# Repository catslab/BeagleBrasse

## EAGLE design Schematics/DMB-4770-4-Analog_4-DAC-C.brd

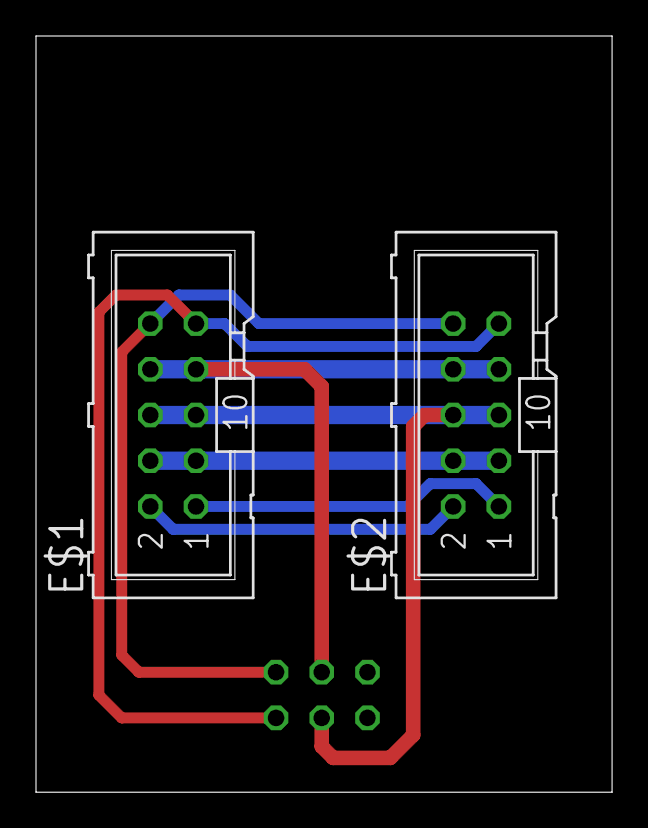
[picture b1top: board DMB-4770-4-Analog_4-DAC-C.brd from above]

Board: 2 copper layers, 32.0 x 42.0 mm, 3 parts (1 on the bottom side), 7 nets.

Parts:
E$1, E$2: ML10
E$3: ML6

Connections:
3V3: E$1.7, E$1.8, E$2.7, E$2.8, E$3.4
5V: E$1.3, E$1.4, E$2.3, E$2.4
GND: E$1.5, E$1.6, E$2.5, E$2.6, E$3.3
S$4: E$1.1, E$2.1
S$5: E$1.2, E$2.2
SCL: E$1.10, E$2.10, E$3.6
SDA: E$1.9, E$2.9, E$3.5

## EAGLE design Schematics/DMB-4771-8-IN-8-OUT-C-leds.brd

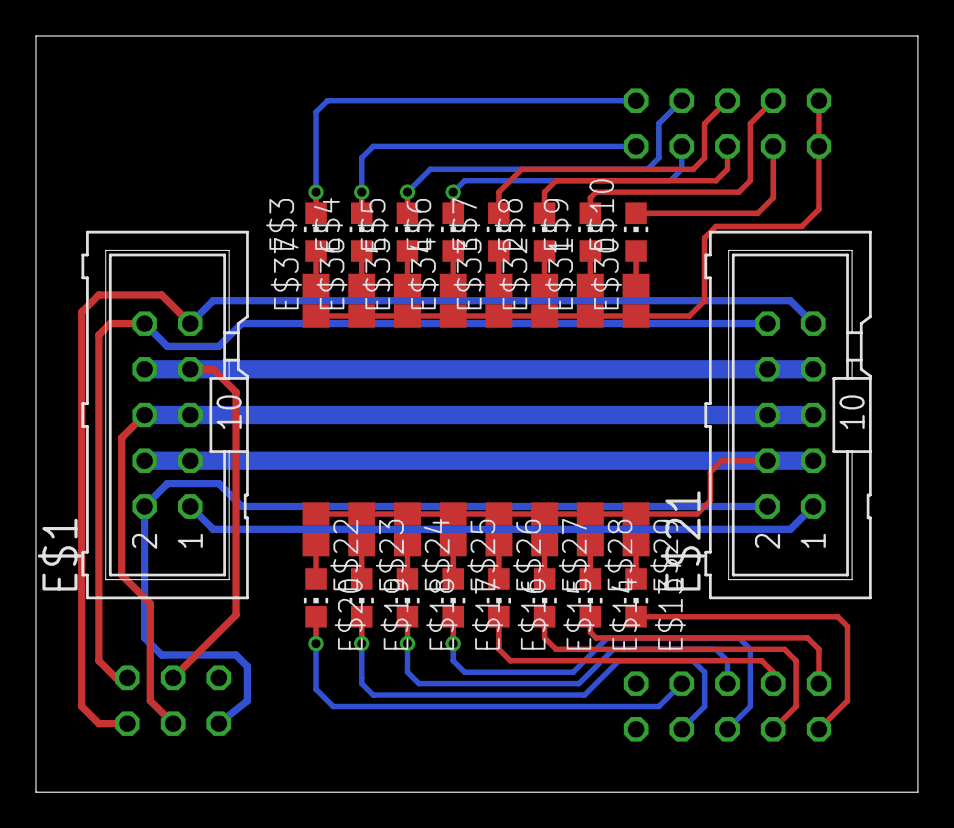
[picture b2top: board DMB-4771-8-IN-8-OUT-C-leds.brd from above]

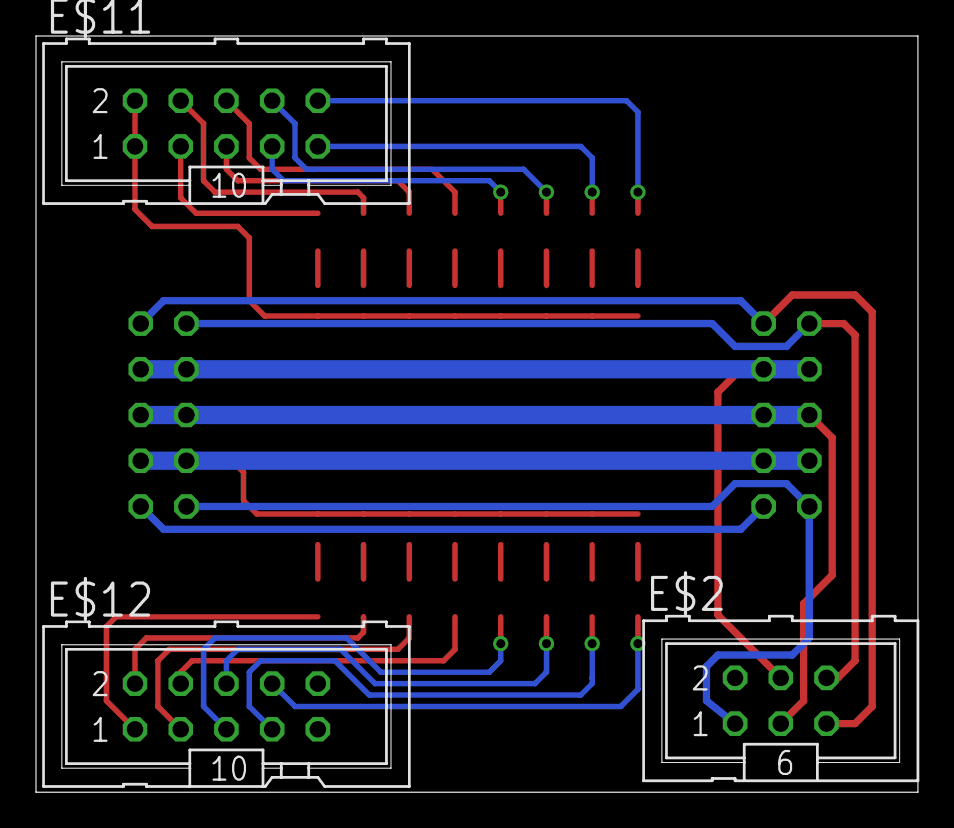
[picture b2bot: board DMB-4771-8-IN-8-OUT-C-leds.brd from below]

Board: 2 copper layers, 49.0 x 42.0 mm, 37 parts (3 on the bottom side), 40 nets.

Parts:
E$1, E$11, E$12, E$21: ML10
E$2: ML6
E$3, E$4, E$5, E$6, E$7, E$8, E$9, E$10, E$13, E$14, E$15, E$16, E$17, E$18, E$19, E$20: CHIP-LED0805
E$22, E$23, E$24, E$25, E$26, E$27, E$28, E$29, E$30, E$31, E$32, E$33, E$34, E$35, E$36, E$37: R0805

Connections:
S$8: E$1.7, E$1.8, E$2.4, E$21.7, E$21.8
S$26: E$1.3, E$1.4, E$21.3, E$21.4, E$22.1, E$23.1, E$24.1, E$25.1, E$26.1, E$27.1, E$28.1, E$29.1
S$27: E$12.8, E$20.C
S$28: E$12.7, E$19.C
S$29: E$12.6, E$18.C
S$34: E$12.5, E$17.C
S$35: E$12.4, E$16.C
S$36: E$12.3, E$15.C
S$37: E$12.2, E$14.C
S$38: E$12.1, E$13.C
S$39: E$20.A, E$22.2
S$40: E$19.A, E$23.2
S$41: E$18.A, E$24.2
S$42: E$17.A, E$25.2
S$43: E$16.A, E$26.2
S$44: E$15.A, E$27.2
S$45: E$14.A, E$28.2
S$46: E$13.A, E$29.2
S$80: E$1.10, E$2.6, E$21.10
S$81: E$3.C, E$11.10
S$83: E$10.A, E$30.2
S$84: E$1.9, E$2.5, E$21.9
S$85: E$9.A, E$31.2
S$86: E$8.A, E$32.2
S$88: E$1.5, E$1.6, E$2.3, E$21.5, E$21.6
S$89: E$7.A, E$33.2
S$90: E$1.2, E$2.1, E$21.2
S$91: E$1.1, E$21.1
S$92: E$6.A, E$34.2
S$93: E$5.A, E$35.2
S$94: E$4.A, E$36.2
S$95: E$3.A, E$37.2
S$96: E$4.C, E$11.9
S$97: E$5.C, E$11.8
S$98: E$6.C, E$11.7
S$99: E$7.C, E$11.6
S$100: E$8.C, E$11.5
S$102: E$9.C, E$11.4
S$103: E$10.C, E$11.3
S$104: E$11.1, E$11.2, E$30.1, E$31.1, E$32.1, E$33.1, E$34.1, E$35.1, E$36.1, E$37.1

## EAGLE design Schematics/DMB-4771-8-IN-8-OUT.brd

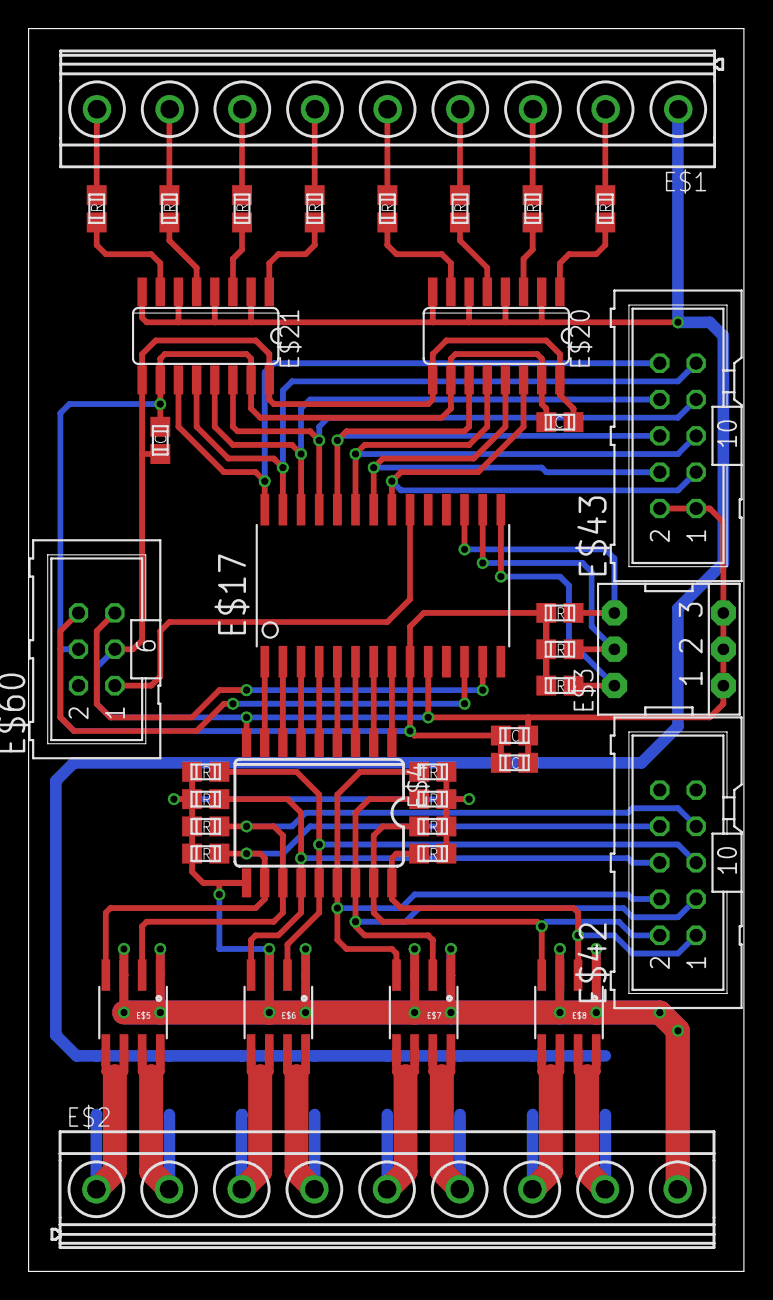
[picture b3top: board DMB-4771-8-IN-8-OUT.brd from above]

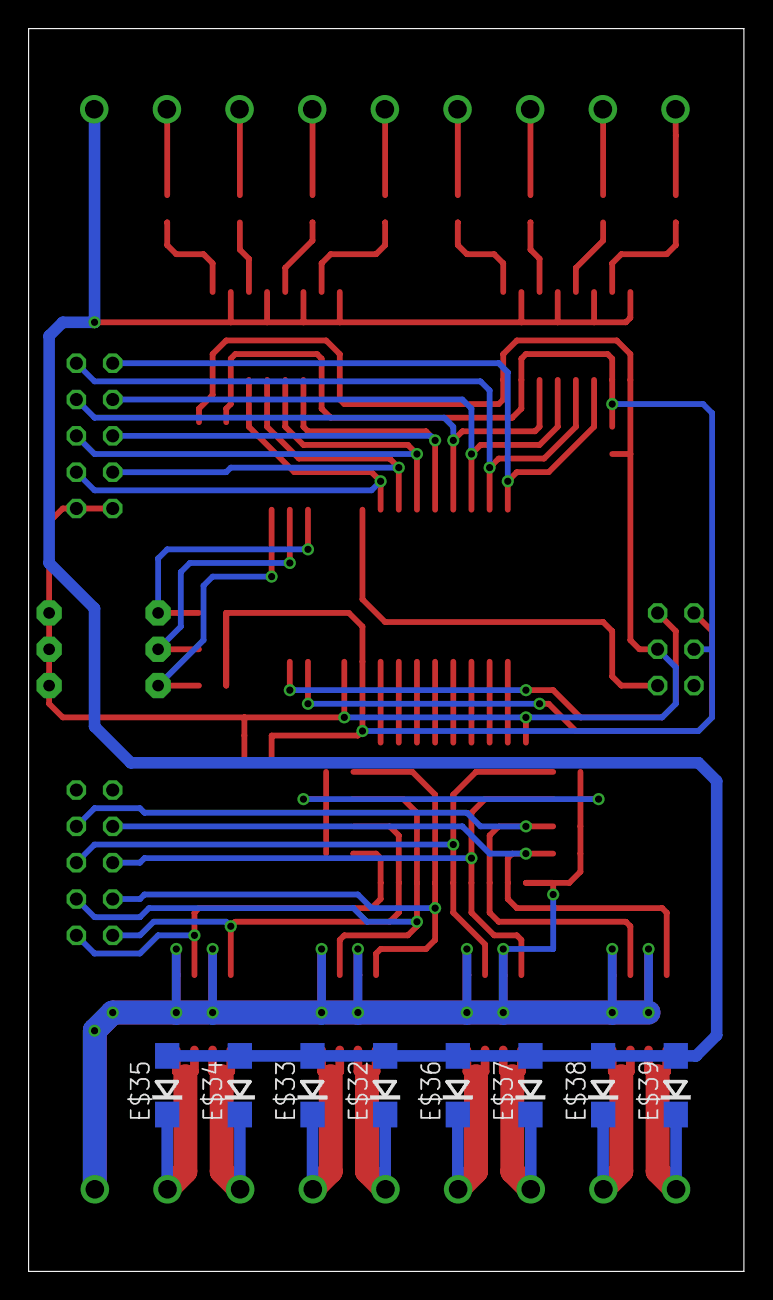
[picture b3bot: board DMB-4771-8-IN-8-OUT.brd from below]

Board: 2 copper layers, 50.0 x 86.9 mm, 45 parts (8 on the bottom side), 58 nets.

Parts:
E$1, E$2: MKDSN1,5/9-5,08
E$3: EPG-03-SMALL
E$4: ULN2803; SO18L
E$5, E$6, E$7, E$8: SOIC8
E$9, E$10, E$11, E$12, E$13, E$14, E$15, E$16, E$18, E$19, E$226: 10K; R0805
E$17: MCP23017; SO28-3
E$20, E$21: ACSL-6400; SO16
E$22, E$23, E$24, E$25, E$26, E$27, E$28, E$29: 1.30K; R0805
E$30, E$40, E$41: 100n; C0805
E$31: 1u; C0805
E$32, E$33, E$34, E$35, E$36, E$37, E$38, E$39: DO214AC
E$42, E$43: ML10
E$60: ML6

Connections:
3V3: E$16.1, E$17.9, E$18.1, E$19.1, E$20.10, E$20.15, E$21.10, E$21.15, E$30.1, E$31.1, E$40.2, E$41.2, E$60.4
GND: E$3.1, E$3.2, E$3.3, E$4.9, E$17.10, E$20.9, E$20.16, E$21.9, E$21.16, E$30.2, E$31.2, E$40.1, E$41.1, E$43.1, E$43.2, E$60.3
INT1: E$17.20, E$60.1
POWER_GND: E$1.1, E$20.2, E$20.4, E$20.6, E$20.8, E$21.2, E$21.4, E$21.6, E$21.8, E$32.A, E$33.A, E$34.A, E$35.A, E$36.A, E$37.A, E$38.A, E$39.A
S$9: E$2.9, E$4.10, E$5.1, E$5.3, E$6.1, E$6.3, E$7.1, E$7.3, E$8.1, E$8.3, E$9.1, E$10.1, E$11.1, E$12.2, E$13.2, E$14.2, E$15.2, E$226.1
S$11: E$2.1, E$5.5, E$5.6, E$39.C
S$13: E$2.2, E$5.7, E$5.8, E$38.C
S$14: E$2.3, E$6.5, E$6.6, E$37.C
S$15: E$17.28, E$21.11, E$43.10
S$16: E$2.5, E$7.5, E$7.6, E$32.C
S$20: E$4.11, E$5.4, E$42.8, E$226.2
S$21: E$4.12, E$5.2, E$9.2, E$42.7
S$23: E$4.13, E$6.4, E$10.2, E$42.6
S$25: E$4.14, E$6.2, E$11.2, E$42.5
S$28: E$4.15, E$7.4, E$12.1, E$42.4
S$29: E$4.16, E$7.2, E$13.1, E$42.3
S$31: E$4.17, E$8.4, E$14.1, E$42.2
S$32: E$4.18, E$8.2, E$15.1, E$42.1
S$33: E$4.8, E$17.1
S$34: E$4.7, E$17.2
S$35: E$4.6, E$17.3
S$38: E$4.5, E$17.4
S$39: E$4.4, E$17.5
S$40: E$4.3, E$17.6
S$41: E$4.2, E$17.7
S$42: E$4.1, E$17.8
S$55: E$3.4, E$17.17, E$18.2
S$59: E$3.5, E$16.2, E$17.16
S$66: E$3.6, E$17.15, E$19.2
S$67: E$2.6, E$7.7, E$7.8, E$33.C
S$68: E$2.7, E$8.5, E$8.6, E$34.C
S$70: E$2.8, E$8.7, E$8.8, E$35.C
S$71: E$2.4, E$6.7, E$6.8, E$36.C
S$74: E$21.7, E$22.1
S$75: E$21.5, E$23.1
S$76: E$21.3, E$24.1
S$77: E$1.9, E$22.2
S$78: E$1.8, E$23.2
S$79: E$1.7, E$24.2
S$80: E$1.6, E$25.2
S$81: E$1.5, E$26.2
S$82: E$1.4, E$27.2
S$83: E$1.3, E$28.2
S$84: E$1.2, E$29.2
S$85: E$21.1, E$25.1
S$86: E$20.7, E$26.1
S$90: E$17.27, E$21.12, E$43.9
S$91: E$17.26, E$21.13, E$43.8
S$92: E$17.25, E$21.14, E$43.7
S$93: E$17.24, E$20.11, E$43.6
S$94: E$17.23, E$20.12, E$43.5
S$95: E$17.22, E$20.13, E$43.4
S$96: E$17.21, E$20.14, E$43.3
S$97: E$20.5, E$27.1
S$98: E$20.3, E$28.1
S$99: E$20.1, E$29.1
SCL: E$17.12, E$60.6
SDA: E$17.13, E$60.5

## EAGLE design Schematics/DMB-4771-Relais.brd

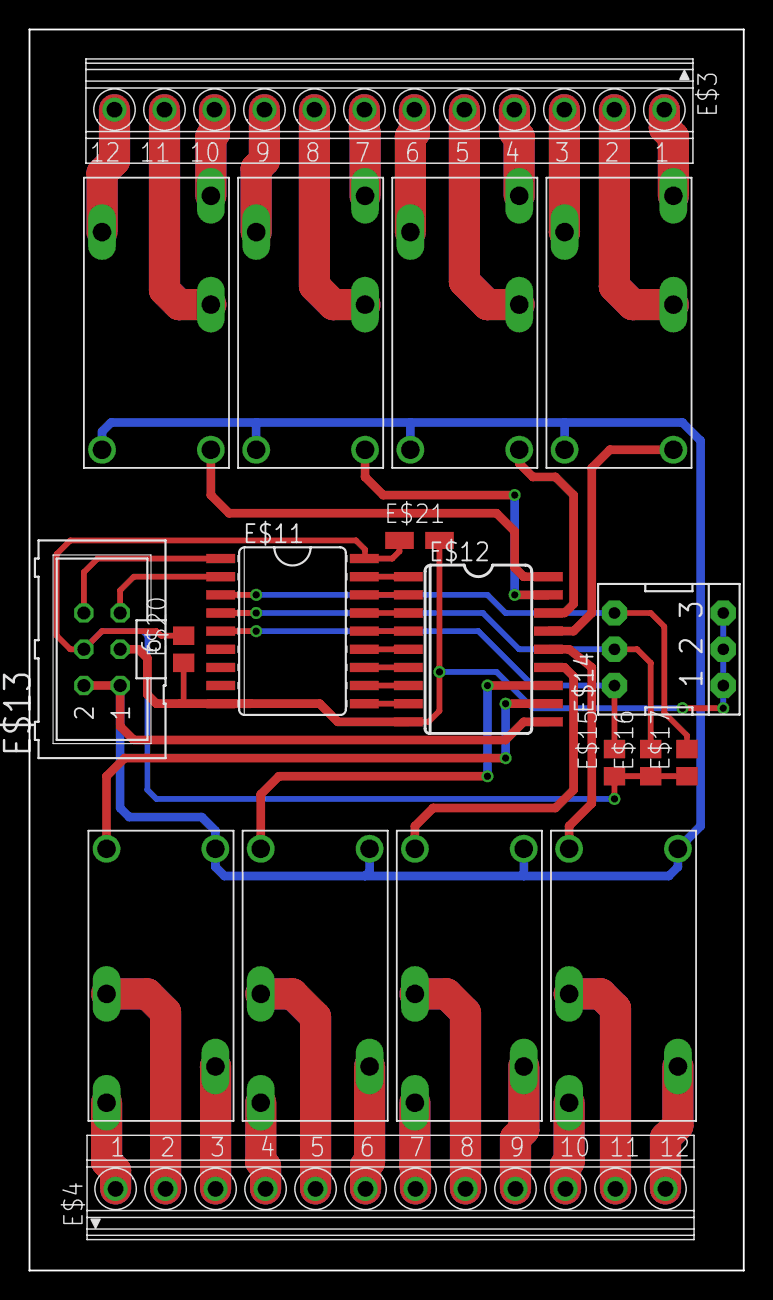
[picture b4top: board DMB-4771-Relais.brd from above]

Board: 2 copper layers, 50.0 x 86.9 mm, 19 parts (0 on the bottom side), 48 nets.

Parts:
E$1, E$2, E$5, E$6, E$7, E$8, E$9, E$10: ALQ105; ALQ
E$3, E$4: 175317
E$11: MCP2308; SO18W
E$12: ULN2803; SO18L
E$13: ML6
E$14: EPG-03-SMALL
E$15, E$16, E$17: 10K; R0805
E$20: 100n; R0805
E$21: 10u; CT3216

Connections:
3V3: E$11.18, E$13.4, E$15.1, E$16.1, E$17.1, E$20.2, E$21.+
5V: E$1.P$1, E$2.P$1, E$5.P$1, E$6.P$1, E$7.P$1, E$8.P$1, E$9.P$1, E$10.P$1, E$12.10, E$13.1, E$13.2
GND: E$11.9, E$12.9, E$13.3, E$14.1, E$14.2, E$14.3, E$20.1, E$21.-
S$8: E$2.P$5, E$3.21
S$9: E$2.P$3, E$3.20
S$10: E$2.P$4, E$3.19
S$11: E$1.P$5, E$3.9
S$13: E$1.P$4, E$3.7
S$14: E$1.P$3, E$3.8
S$15: E$3.6, E$6.P$5
S$16: E$3.5, E$6.P$3
S$17: E$3.4, E$6.P$4
S$18: E$3.3, E$5.P$5
S$19: E$3.2, E$5.P$3
S$20: E$3.1, E$5.P$4
S$21: E$4.21, E$8.P$5
S$22: E$4.20, E$8.P$3
S$23: E$4.19, E$8.P$4
S$24: E$4.8, E$7.P$3
S$25: E$4.6, E$10.P$5
S$26: E$4.5, E$10.P$3
S$27: E$4.3, E$9.P$5
S$28: E$4.2, E$9.P$3
S$29: E$4.9, E$7.P$5
S$30: E$4.7, E$7.P$4
S$31: E$4.4, E$10.P$4
S$32: E$4.1, E$9.P$4
S$61: E$11.17, E$12.1
S$62: E$11.16, E$12.2
S$63: E$11.15, E$12.3
S$64: E$11.14, E$12.4
S$65: E$11.13, E$12.5
S$66: E$11.12, E$12.6
S$67: E$11.11, E$12.7
S$68: E$11.10, E$12.8
S$70: E$2.P$2, E$12.18
S$71: E$1.P$2, E$12.17
S$72: E$6.P$2, E$12.16
S$73: E$5.P$2, E$12.15
S$74: E$8.P$2, E$12.14
S$75: E$7.P$2, E$12.13
S$76: E$10.P$2, E$12.12
S$77: E$9.P$2, E$12.11
S$78: E$11.3, E$14.4, E$17.2
S$79: E$11.4, E$14.5, E$16.2
S$80: E$11.5, E$14.6, E$15.2
SCL: E$11.1, E$13.6
SDA: E$11.2, E$13.5

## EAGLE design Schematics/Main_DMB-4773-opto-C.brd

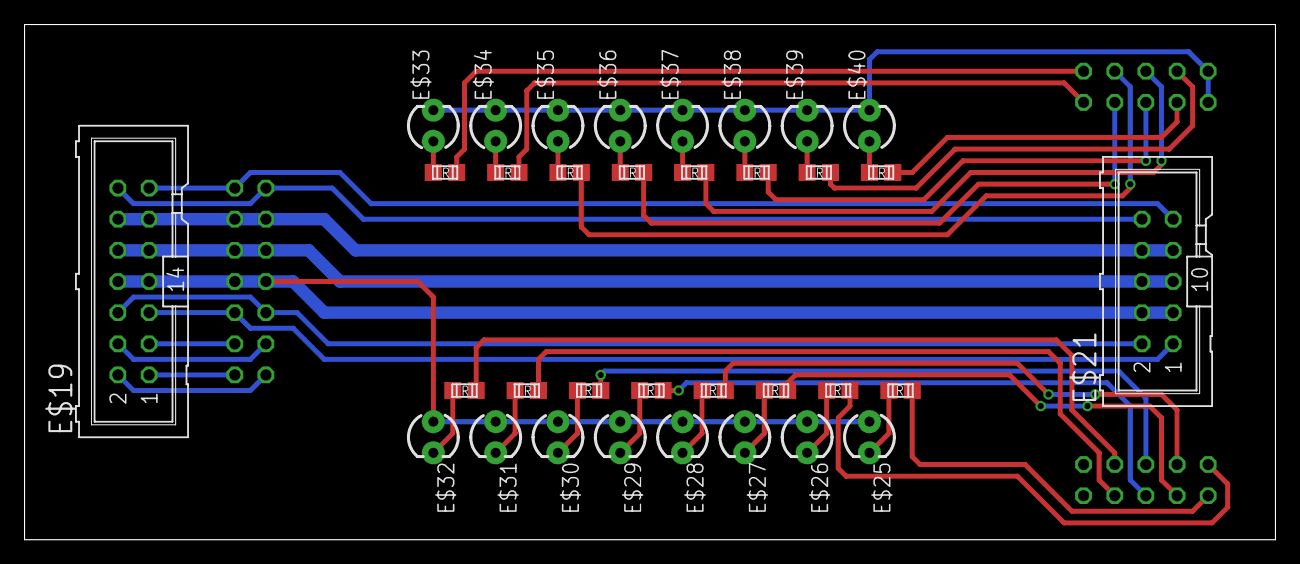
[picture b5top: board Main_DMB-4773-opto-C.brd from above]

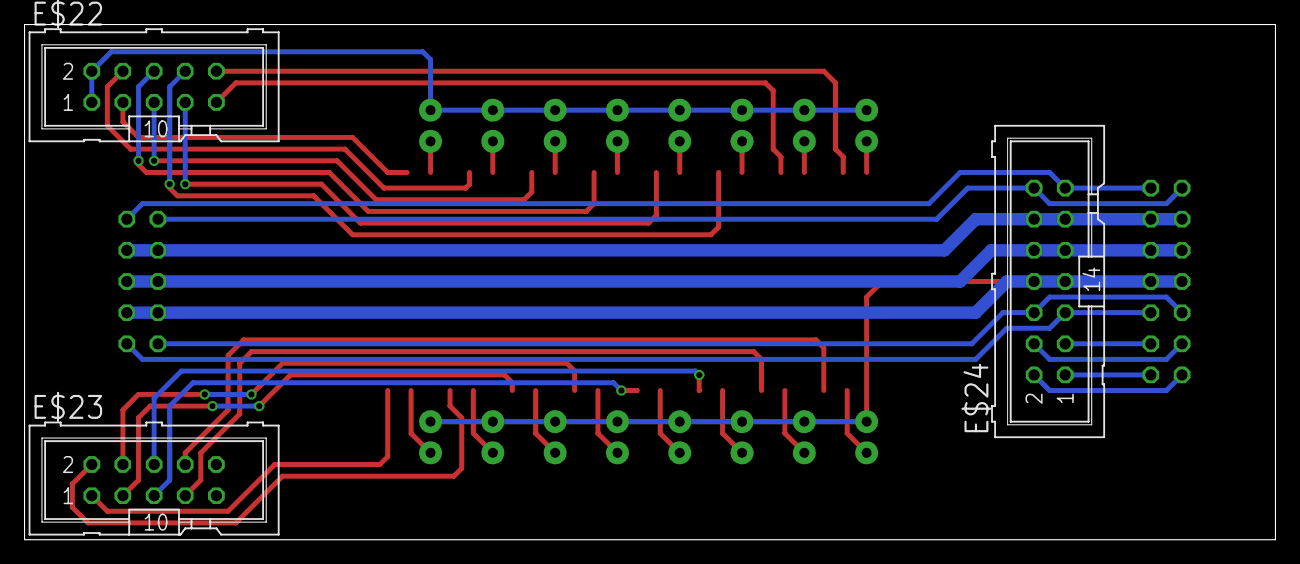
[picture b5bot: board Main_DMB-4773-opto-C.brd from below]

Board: 2 copper layers, 102.0 x 42.0 mm, 37 parts (3 on the bottom side), 44 nets.

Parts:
E$19, E$24: ML14
E$21, E$22, E$23: ML10
E$25, E$26, E$27, E$28, E$29, E$30, E$31, E$32, E$33, E$34, E$35, E$36, E$37, E$38, E$39, E$40: LED3MM
E$41, E$42, E$43, E$44, E$45, E$46, E$47, E$48, E$51, E$75, E$93, E$94, E$95, E$96, E$97, E$98: 470; R0805

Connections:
S$86: E$19.11, E$19.12, E$21.7, E$21.8, E$24.11, E$24.12
S$88: E$19.9, E$19.10, E$21.5, E$21.6, E$24.9, E$24.10
S$90: E$19.6, E$21.2, E$24.6
S$91: E$19.5, E$21.1, E$24.5
S$92: E$19.4, E$24.4
S$93: E$19.3, E$24.3
S$94: E$19.2, E$24.2
S$95: E$19.1, E$24.1
S$96: E$23.4, E$45.1
S$97: E$19.7, E$19.8, E$21.3, E$21.4, E$24.7, E$24.8, E$25.A, E$26.A, E$27.A, E$28.A, E$29.A, E$30.A, E$31.A, E$32.A
S$98: E$32.K, E$41.1
S$100: E$23.8, E$41.2
S$103: E$31.K, E$42.1
S$104: E$23.7, E$42.2
S$106: E$30.K, E$43.2
S$107: E$29.K, E$44.2
S$109: E$23.6, E$43.1
S$110: E$23.5, E$44.1
S$111: E$23.3, E$46.1
S$112: E$23.2, E$47.1
S$113: E$23.1, E$48.1
S$115: E$28.K, E$45.2
S$117: E$27.K, E$46.2
S$118: E$26.K, E$47.2
S$121: E$25.K, E$48.2
S$122: E$22.10, E$51.2
S$123: E$22.9, E$75.2
S$124: E$22.8, E$93.2
S$125: E$22.7, E$94.2
S$127: E$22.6, E$95.2
S$128: E$22.5, E$96.2
S$129: E$22.4, E$97.2
S$130: E$22.3, E$98.2
S$131: E$22.1, E$22.2, E$33.K, E$34.K, E$35.K, E$36.K, E$37.K, E$38.K, E$39.K, E$40.K
S$135: E$33.A, E$51.1
S$136: E$34.A, E$75.1
S$137: E$35.A, E$93.1
S$138: E$36.A, E$94.1
S$139: E$37.A, E$95.1
S$140: E$38.A, E$96.1
S$142: E$39.A, E$97.1
S$144: E$40.A, E$98.1
SCL: E$19.14, E$21.10, E$24.14
SDA: E$19.13, E$21.9, E$24.13

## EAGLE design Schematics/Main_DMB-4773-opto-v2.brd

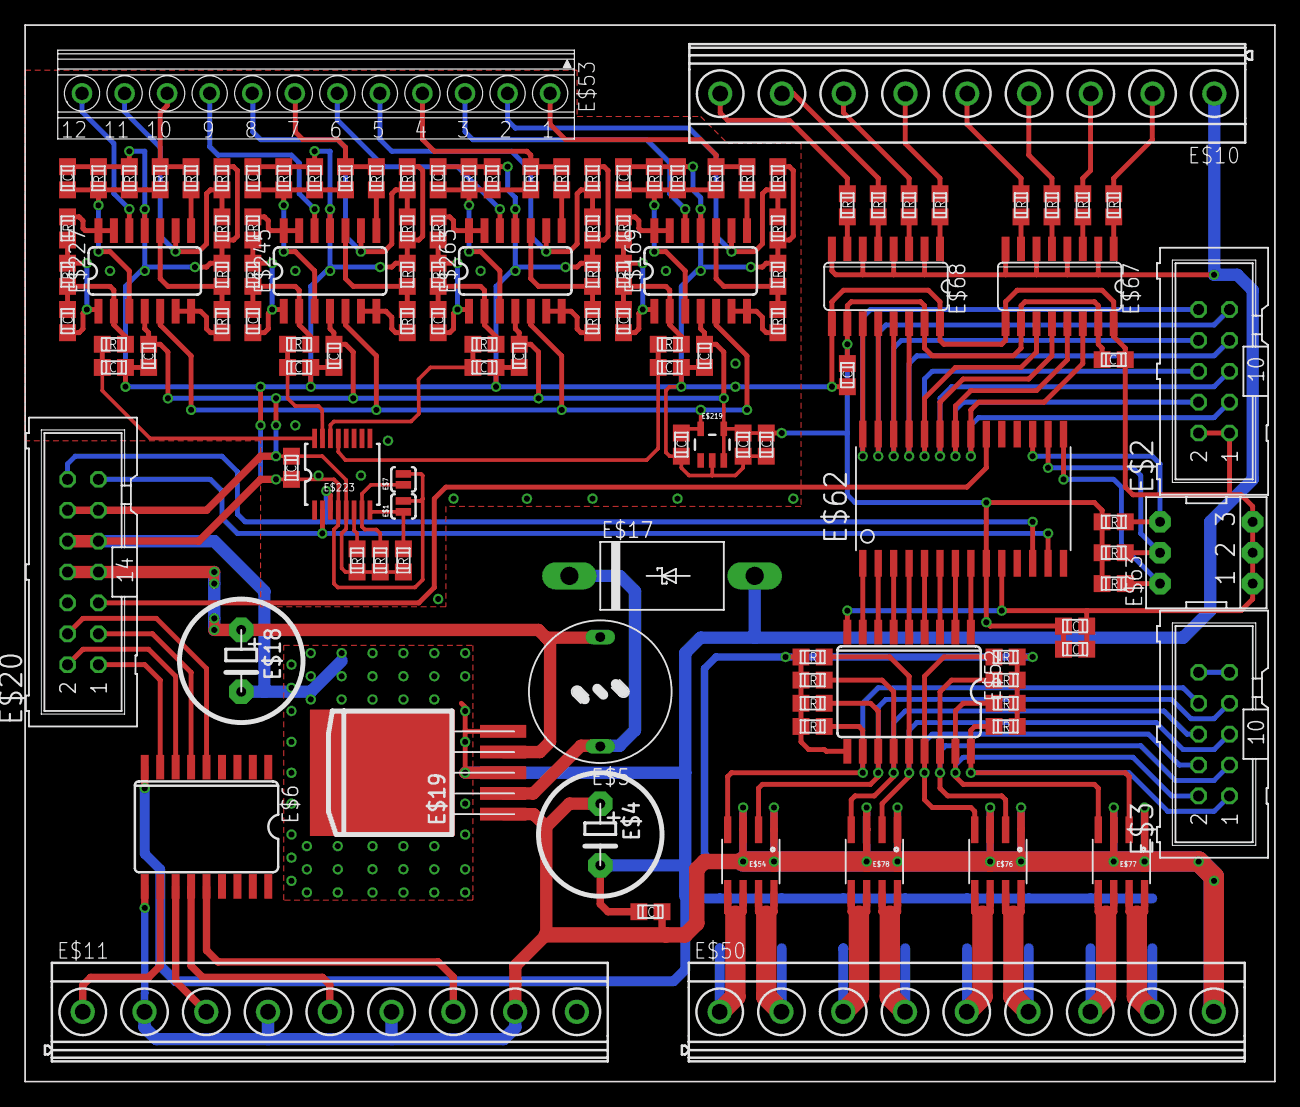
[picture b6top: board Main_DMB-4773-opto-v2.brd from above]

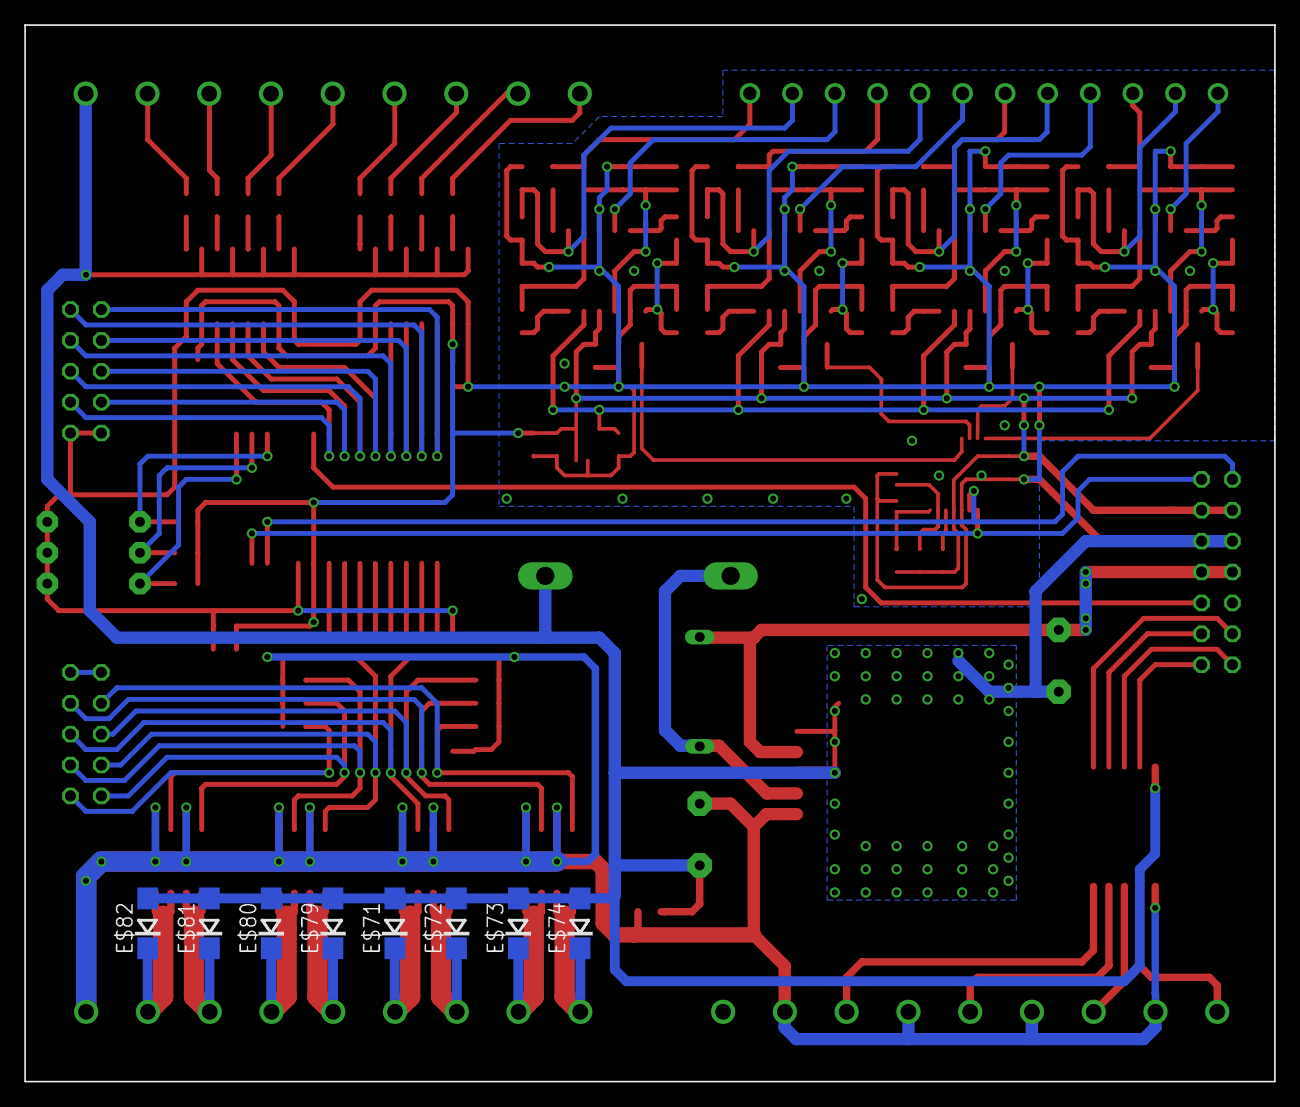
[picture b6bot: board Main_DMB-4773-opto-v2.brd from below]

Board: 2 copper layers, 102.8 x 86.9 mm, 129 parts (8 on the bottom side), 116 nets.

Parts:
E$1, E$7: SJ_2S-NO
E$2, E$3: ML10
E$4, E$18: CE02A
E$5: RLB1314
E$6, E$52: ULN2803; SO18L
E$9, E$13, E$69, E$83, E$84: 100n; C0805
E$10, E$11, E$50: MKDSN1,5/9-5,08
E$17: DO201T15
E$19: TO263-5
E$20: ML14
E$49, E$55, E$56, E$57, E$58, E$59, E$60, E$61, E$64, E$65, E$66, E$224, E$225, E$226: 10K; R0805
E$53: 175317
E$54, E$76, E$77, E$78: SOIC8
E$62: MCP23017; SO28-3
E$63: EPG-03-SMALL
E$67, E$68: ACSL-6400; SO16
E$70: 1u; C0805
E$71, E$72, E$73, E$74, E$79, E$80, E$81, E$82: DO214AC
E$85, E$86, E$87, E$88, E$89, E$90, E$91, E$92: 1.30K; R0805
E$169, E$227, E$245, E$263: SOIC-14
E$170, E$175, E$184, E$185, E$220, E$221, E$228, E$233, E$243, E$246, E$251, E$261, E$264, E$269, E$279: 0.1; C0805
E$171, E$179, E$229, E$237, E$247, E$255, E$265, E$273: 1K; R0805
E$172, E$173, E$230, E$231, E$248, E$249, E$266, E$267: 2K; R0805
E$174, E$178, E$232, E$236, E$250, E$254, E$268, E$272: 39.2K; R0805
E$176, E$234, E$252, E$270: 1.91K; R0805
E$177, E$235, E$253, E$271: 100; R0805
E$180, E$238, E$256, E$274: 26.7K; R0805
E$181, E$239, E$257, E$275: 1.1K; R0805
E$182, E$240, E$258, E$276: 4.7n; C0805
E$183, E$241, E$259, E$277: 51; R0805
E$219: SOT23-5
E$223: AD5316R; TSSOP16

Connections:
+5V: E$5.2, E$18.+, E$19.4, E$20.7, E$20.8
GND: E$1.2, E$2.1, E$2.2, E$4.-, E$6.9, E$7.2, E$9.2, E$10.1, E$13.1, E$17.A, E$18.-, E$19.3, E$19.5, E$20.9, E$20.10, E$52.9, E$62.10, E$63.1, E$63.2, E$63.3, E$67.2, E$67.4, E$67.6, E$67.8, E$67.9, E$67.16, E$68.2, E$68.4, E$68.6, E$68.8, E$68.9, E$68.16, E$69.2, E$70.2, E$71.A, E$72.A, E$73.A, E$74.A, E$79.A, E$80.A, E$81.A, E$82.A, E$83.1, E$84.1, E$169.11, E$173.1, E$174.1, E$175.2, E$176.1, E$177.2, E$181.2, E$182.1, E$184.1, E$185.2, E$219.2, E$220.1, E$221.1, E$223.4, E$227.11, E$231.1, E$232.1, E$233.2, E$234.1, E$235.2, E$239.2, E$240.1, E$243.2, E$245.11, E$249.1, E$250.1, E$251.2, E$252.1, E$253.2, E$257.2, E$258.1, E$261.2, E$263.11, E$267.1, E$268.1, E$269.2, E$270.1, E$271.2, E$275.2, E$276.1, E$279.2
S$8: E$10.9, E$85.2
S$11: E$53.1, E$171.1, E$172.1
S$26: E$6.11, E$11.1
S$27: E$6.12, E$11.3
S$28: E$6.13, E$11.5
S$29: E$6.14, E$11.7
S$34: E$1.1, E$223.8, E$224.1
S$35: E$6.6, E$20.3
S$36: E$6.5, E$20.4
S$37: E$6.7, E$20.2
S$38: E$6.8, E$20.1
S$39: E$10.8, E$86.2
S$40: E$10.7, E$87.2
S$41: E$10.6, E$88.2
S$42: E$10.5, E$89.2
S$43: E$10.4, E$90.2
S$44: E$10.3, E$91.2
S$45: E$10.2, E$92.2
S$46: E$68.7, E$85.1
S$81: E$4.+, E$6.10, E$11.2, E$11.4, E$11.6, E$11.8, E$13.2, E$19.1, E$49.1, E$50.9, E$52.10, E$54.1, E$54.3, E$55.1, E$56.1, E$57.1, E$58.2, E$59.2, E$60.2, E$61.2, E$76.1, E$76.3, E$77.1, E$77.3, E$78.1, E$78.3
S$83: E$5.1, E$17.C, E$19.2
S$99: E$169.8, E$171.2
S$102: E$169.6, E$169.7, E$180.2
S$105: E$53.2, E$169.9, E$176.2, E$177.1
S$108: E$169.1, E$170.1, E$178.1, E$179.1
S$114: E$169.2, E$170.2, E$178.2, E$183.1
S$120: E$169.13, E$169.14, E$179.2
S$126: E$169.10, E$180.1, E$181.1
S$132: E$169.3, E$172.2, E$173.2, E$174.2, E$175.1
S$133: E$53.3, E$169.12
S$134: E$182.2, E$183.2, E$223.13
S$145: E$3.9, E$3.10
S$151: E$169.5, E$184.2, E$219.5, E$227.5, E$245.5, E$263.5
S$152: E$3.8, E$49.2, E$52.11, E$54.4
S$153: E$3.7, E$52.12, E$54.2, E$55.2
S$158: E$3.6, E$52.13, E$56.2, E$78.4
S$159: E$3.5, E$52.14, E$57.2, E$78.2
S$160: E$3.4, E$52.15, E$58.1, E$76.4
S$162: E$3.3, E$52.16, E$59.1, E$76.2
S$163: E$3.2, E$52.17, E$60.1, E$77.4
S$164: E$3.1, E$52.18, E$61.1, E$77.2
S$166: E$52.8, E$62.1
S$167: E$52.7, E$62.2
S$168: E$52.6, E$62.3
S$169: E$52.5, E$62.4
S$170: E$52.4, E$62.5
S$171: E$52.3, E$62.6
S$172: E$52.2, E$62.7
S$173: E$52.1, E$62.8
S$182: E$2.10, E$62.28, E$68.11
S$183: E$2.9, E$62.27, E$68.12
S$184: E$2.8, E$62.26, E$68.13
S$185: E$2.7, E$62.25, E$68.14
S$186: E$2.6, E$62.24, E$67.11
S$187: E$2.5, E$62.23, E$67.12
S$188: E$2.4, E$62.22, E$67.13
S$189: E$2.3, E$62.21, E$67.14
S$190: E$20.5, E$62.20
S$191: E$62.17, E$63.4, E$65.2
S$192: E$62.16, E$63.5, E$64.2
S$193: E$62.15, E$63.6, E$66.2
S$194: E$50.1, E$54.5, E$54.6, E$74.C
S$195: E$53.19, E$229.1, E$230.1
S$196: E$227.8, E$229.2
S$197: E$227.6, E$227.7, E$238.2
S$198: E$53.20, E$227.9, E$234.2, E$235.1
S$199: E$227.1, E$228.1, E$236.1, E$237.1
S$200: E$227.2, E$228.2, E$236.2, E$241.1
S$201: E$227.13, E$227.14, E$237.2
S$202: E$227.10, E$238.1, E$239.1
S$203: E$50.2, E$54.7, E$54.8, E$73.C
S$204: E$227.3, E$230.2, E$231.2, E$232.2, E$233.1
S$205: E$53.21, E$227.12
S$206: E$223.16, E$240.2, E$241.2
S$207: E$50.5, E$76.5, E$76.6, E$79.C
S$208: E$50.6, E$76.7, E$76.8, E$80.C
S$209: E$53.7, E$247.1, E$248.1
S$210: E$245.8, E$247.2
S$211: E$245.6, E$245.7, E$256.2
S$212: E$53.8, E$245.9, E$252.2, E$253.1
S$213: E$245.1, E$246.1, E$254.1, E$255.1
S$214: E$245.2, E$246.2, E$254.2, E$259.1
S$215: E$245.13, E$245.14, E$255.2
S$216: E$245.10, E$256.1, E$257.1
S$217: E$50.7, E$77.5, E$77.6, E$81.C
S$218: E$245.3, E$248.2, E$249.2, E$250.2, E$251.1
S$219: E$53.9, E$245.12
S$220: E$223.15, E$258.2, E$259.2
S$221: E$50.8, E$77.7, E$77.8, E$82.C
S$222: E$50.3, E$72.C, E$78.5, E$78.6
S$223: E$53.4, E$265.1, E$266.1
S$224: E$263.8, E$265.2
S$225: E$263.6, E$263.7, E$274.2
S$226: E$53.5, E$263.9, E$270.2, E$271.1
S$227: E$263.1, E$264.1, E$272.1, E$273.1
S$228: E$263.2, E$264.2, E$272.2, E$277.1
S$229: E$263.13, E$263.14, E$273.2
S$230: E$263.10, E$274.1, E$275.1
S$231: E$223.6, E$226.1
S$232: E$263.3, E$266.2, E$267.2, E$268.2, E$269.1
S$233: E$53.6, E$263.12
S$234: E$223.14, E$276.2, E$277.2
S$235: E$7.1, E$223.7, E$225.1
S$236: E$50.4, E$71.C, E$78.7, E$78.8
S$240: E$68.5, E$86.1
S$241: E$68.3, E$87.1
S$242: E$68.1, E$88.1
S$243: E$67.7, E$89.1
S$244: E$67.5, E$90.1
S$245: E$67.3, E$91.1
S$246: E$67.1, E$92.1
SCL: E$20.14, E$62.12, E$223.3
SDA: E$20.13, E$62.13, E$223.2
VCC: E$9.1, E$20.11, E$20.12, E$62.9, E$64.1, E$65.1, E$66.1, E$67.10, E$67.15, E$68.10, E$68.15, E$69.1, E$70.1, E$83.2, E$84.2, E$169.4, E$185.1, E$219.3, E$219.4, E$220.2, E$221.2, E$223.5, E$224.2, E$225.2, E$226.2, E$227.4, E$243.1, E$245.4, E$261.1, E$263.4, E$279.1

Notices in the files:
parts and their libraries:
SparkFun-PowerIC: Licensing: Creative Commons ShareAlike 4.0 International - https://creativecommons.org/licenses/by-sa/4.0
